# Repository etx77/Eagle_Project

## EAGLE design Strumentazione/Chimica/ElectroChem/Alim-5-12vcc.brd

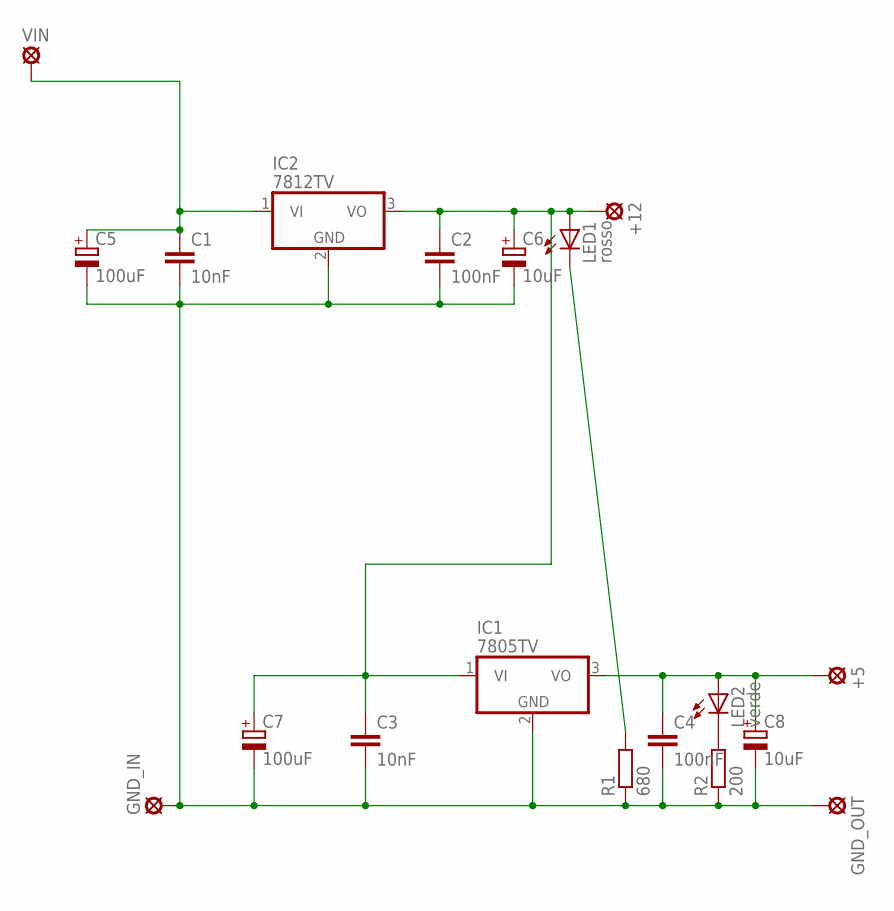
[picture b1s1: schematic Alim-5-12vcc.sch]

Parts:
+5, +12: SE14
C1, C3: 10nF; C050-025X075
C2, C4: 100nF; C050-025X075
C5, C7: 100uF; E2,5-6
C6, C8: 10uF; E2,5-6
GND_IN: SE14
GND_OUT: SE14
IC1: 7805TV; TO220V
IC2: 7812TV; TO220V
LED1: rosso; LED5MM
LED2: verde; LED5MM
R1: 680; 0204/7
R2: 200; 0204/7
VIN: SE14

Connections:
unnamed: C1.1, C5.+, IC2.1 (VI), VIN.MP
unnamed: +12.MP, C2.1, C3.1, C6.+, C7.+, IC1.1 (VI), IC2.3 (VO), LED1.A
unnamed: C1.2, C2.2, C3.2, C4.2, C5.-, C6.-, C7.-, C8.-, GND_IN.MP, GND_OUT.MP, IC1.2 (GND), IC2.2 (GND), R1.1, R2.1
unnamed: LED1.K (C), R1.2
unnamed: +5.MP, C4.1, C8.+, IC1.3 (VO), LED2.A
unnamed: LED2.K (C), R2.2

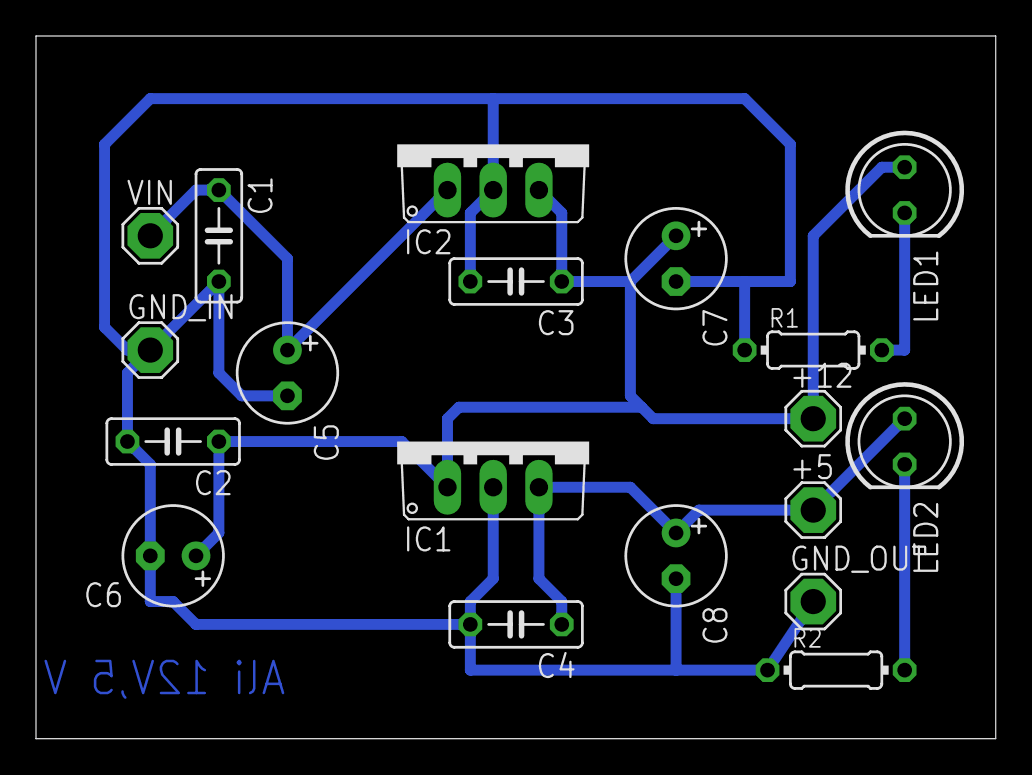
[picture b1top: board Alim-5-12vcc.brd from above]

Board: 2 copper layers, 53.3 x 39.0 mm, 19 parts (0 on the bottom side), 6 nets.

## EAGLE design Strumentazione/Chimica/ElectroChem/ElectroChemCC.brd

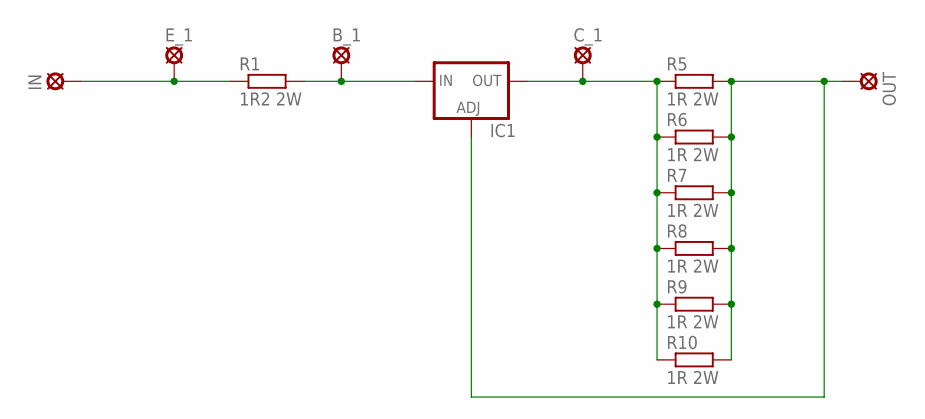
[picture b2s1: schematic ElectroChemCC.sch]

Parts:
B_1: SE14
C_1: SE14
E_1: SE14
IC1: LM317TS; 317TS
IN: SE14
OUT: SE14
R1: 1R2 2W; 0207/10
R5, R6, R7, R8, R9, R10: 1R 2W; 0617/22

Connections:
unnamed: IC1.1 (ADJ), OUT.MP, R5.2, R6.2, R7.2, R8.2, R9.2, R10.2
unnamed: E_1.MP, IN.MP, R1.1
unnamed: C_1.MP, IC1.2 (OUT), R5.1, R6.1, R7.1, R8.1, R9.1, R10.1
unnamed: B_1.MP, IC1.3 (IN), R1.2

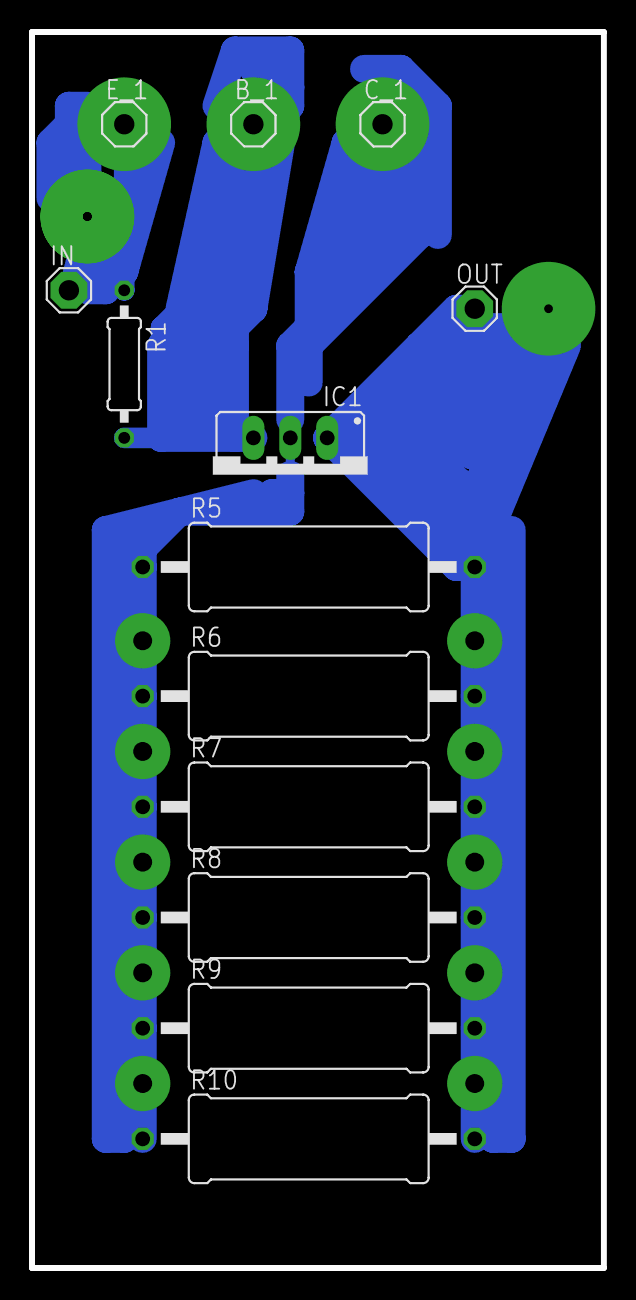
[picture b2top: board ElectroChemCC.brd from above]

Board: 2 copper layers, 39.4 x 85.1 mm, 13 parts (0 on the bottom side), 4 nets.

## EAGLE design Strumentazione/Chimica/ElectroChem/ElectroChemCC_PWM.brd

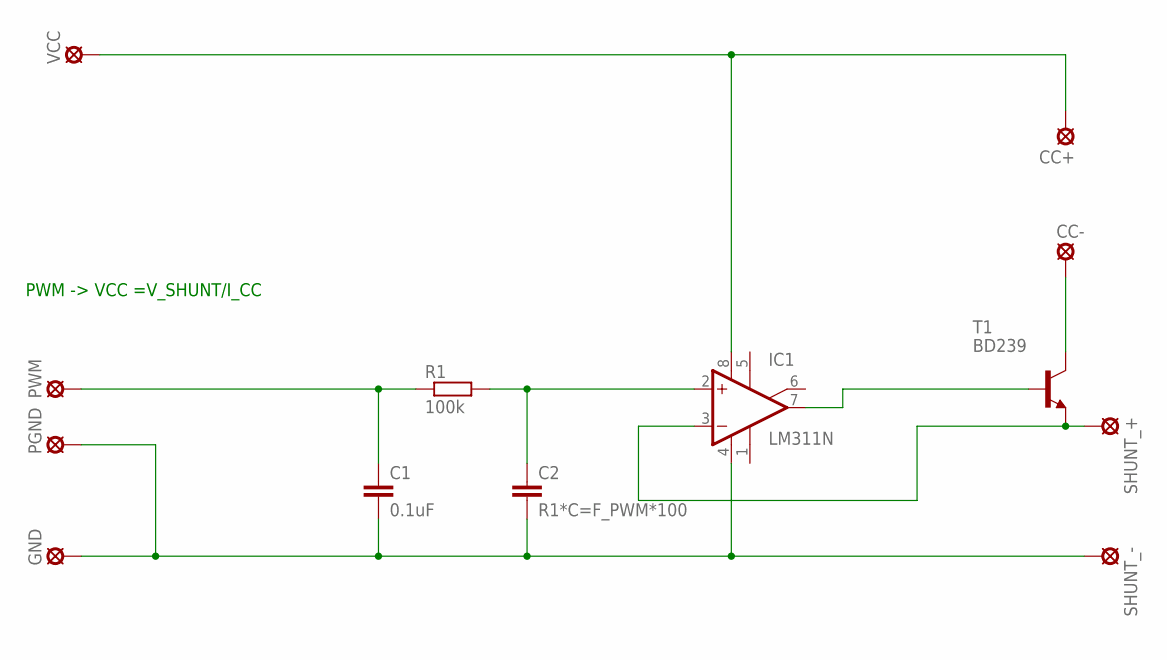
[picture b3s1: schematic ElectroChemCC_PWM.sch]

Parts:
C1: 0.1uF; C050-025X075
C2: R1*C=F_PWM*100; C050-025X075
CC+: LSP10
CC-: LSP10
GND: LSP10
IC1: LM311N; DIL08
PGND: LSP10
PWM: LSP10
R1: 100k; 0207/10
SHUNT_+: LSP10
SHUNT_-: LSP10
T1: BD239; TO220
VCC: LSP10

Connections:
unnamed: CC+.MP, IC1.8 (V+), VCC.MP
unnamed: C1.2, C2.2, GND.MP, IC1.4 (V-), PGND.MP, SHUNT_-.MP
unnamed: C1.1, PWM.MP, R1.1
unnamed: C2.1, IC1.2 (+IN), R1.2
unnamed: IC1.7 (OUT), T1.1 (B)
unnamed: CC-.MP, T1.2 (C)
unnamed: IC1.3 (-IN), SHUNT_+.MP, T1.3 (E)

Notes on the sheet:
PWM -> VCC =V_SHUNT/I_CC

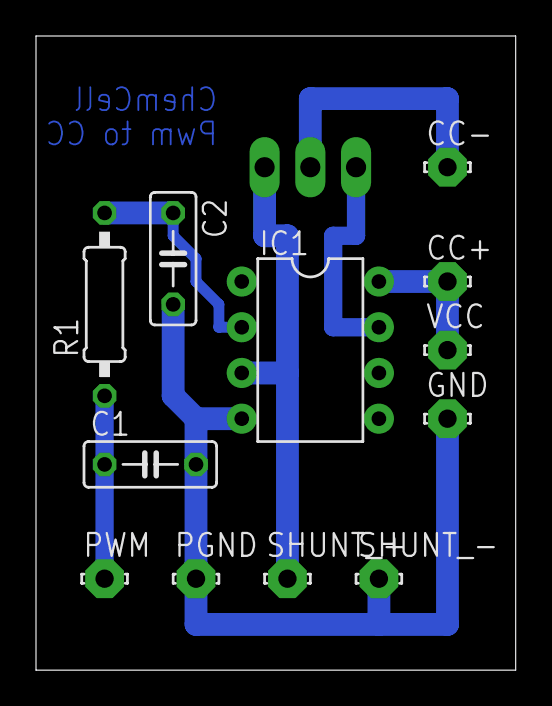
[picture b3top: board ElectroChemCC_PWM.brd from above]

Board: 2 copper layers, 26.6 x 35.2 mm, 13 parts (1 on the bottom side), 7 nets.

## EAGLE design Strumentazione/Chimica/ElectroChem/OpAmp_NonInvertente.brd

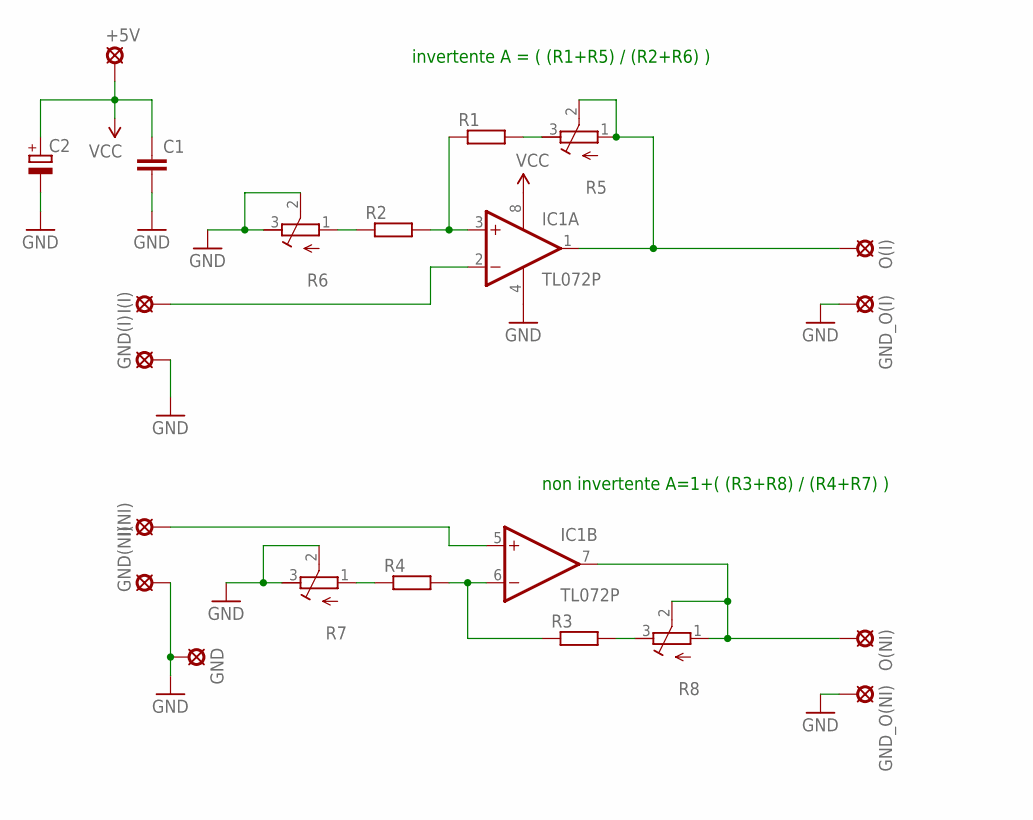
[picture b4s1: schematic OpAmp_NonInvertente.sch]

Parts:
+5V: LSP10
C1: C-EU025-024X044; C025-024X044
C2: CPOL-EUE2.5-6; E2,5-6
GND: LSP10
GND(I): LSP10
GND(NI): LSP10
GND_O(I): LSP10
GND_O(NI): LSP10
I(I): LSP10
I(NI): LSP10
IC1: TL072P; DIL08
O(I): LSP10
O(NI): LSP10
R1, R2, R3, R4: R-EU_0309/10; 0309/10
R5, R6, R7, R8: R-TRIMM3339P; RTRIM3339P

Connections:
GND: C1.2, C2.-, GND.MP, GND(I).MP, GND(NI).MP, GND_O(I).MP, GND_O(NI).MP, IC1.4 (V-), R6.2 (S), R6.3 (E), R7.2 (S), R7.3 (E)
unnamed: R2.1, R6.1 (A)
unnamed: IC1.3 (+IN), R1.1, R2.2
unnamed: R1.2, R5.3 (E)
unnamed: IC1.1 (OUT), O(I).MP, R5.1 (A), R5.2 (S)
unnamed: IC1.6 (-IN), R3.1, R4.2
unnamed: R4.1, R7.1 (A)
unnamed: R3.2, R8.3 (E)
unnamed: IC1.7 (OUT), O(NI).MP, R8.1 (A), R8.2 (S)
unnamed: I(NI).MP, IC1.5 (+IN)
unnamed: I(I).MP, IC1.2 (-IN)
VCC: +5V.MP, C1.1, C2.+, IC1.8 (V+)

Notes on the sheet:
invertente A = ( (R1+R5) / (R2+R6) )
non invertente A=1+( (R3+R8) / (R4+R7) )

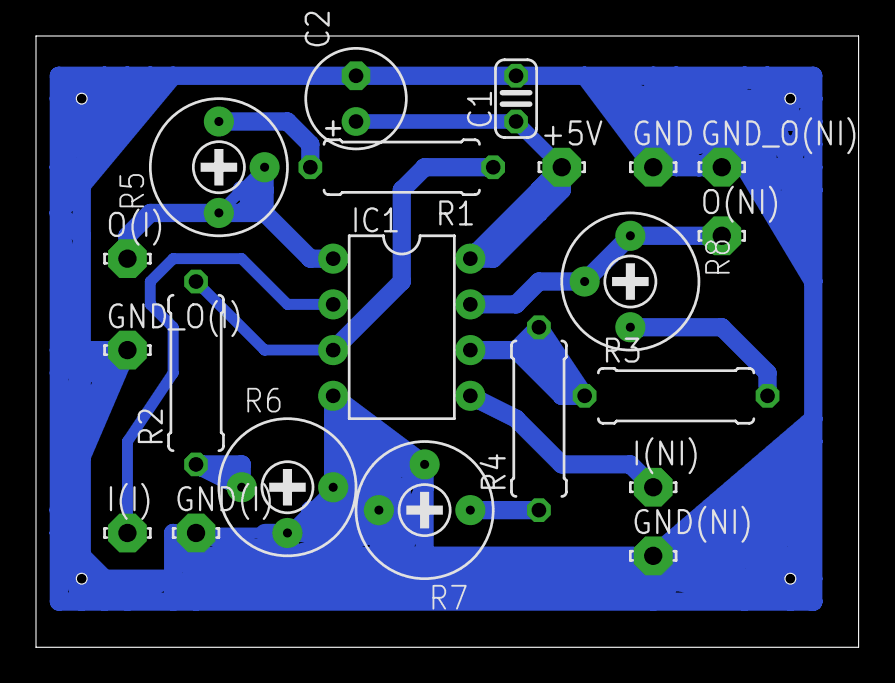
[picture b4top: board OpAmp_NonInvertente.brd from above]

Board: 2 copper layers, 45.7 x 34.0 mm, 21 parts (0 on the bottom side), 12 nets.

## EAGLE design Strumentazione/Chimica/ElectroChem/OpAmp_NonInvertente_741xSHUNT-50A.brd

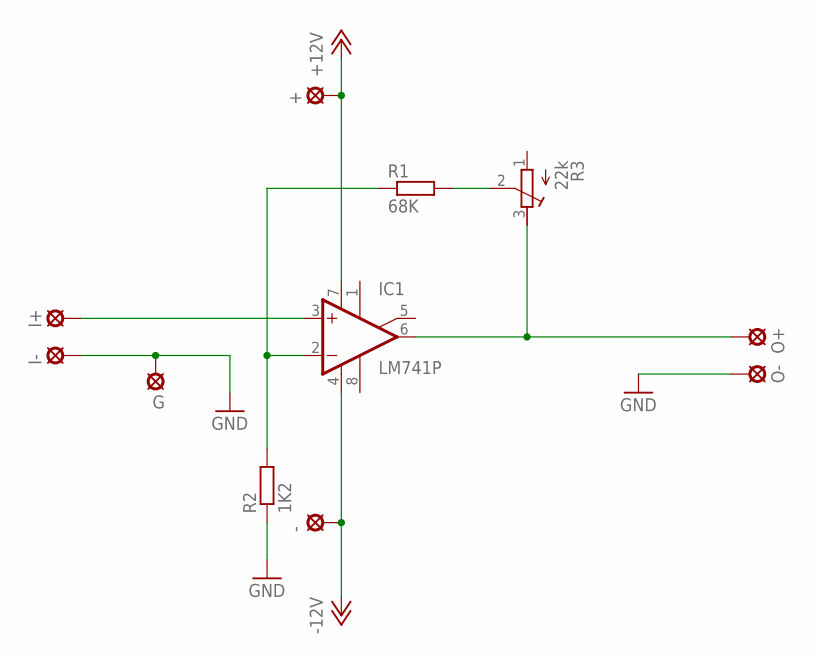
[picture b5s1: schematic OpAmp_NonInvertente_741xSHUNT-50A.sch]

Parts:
+: LSP10
-: LSP10
G: LSP10
I+: LSP10
I-: LSP10
IC1: LM741P; DIL08
O+: LSP10
O-: LSP10
R1: 68K; 0207/12
R2: 1K2; 0207/12
R3: 22k; RTRIM3339P

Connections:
+12V: +.MP, IC1.7 (V+)
-12V: -.MP, IC1.4 (V-)
GND: G.MP, I-.MP, O-.MP, R2.1
unnamed: IC1.2 (-IN), R1.1, R2.2
unnamed: R1.2, R3.2 (S)
unnamed: IC1.6 (OUT), O+.MP, R3.3 (E)
unnamed: I+.MP, IC1.3 (+IN)

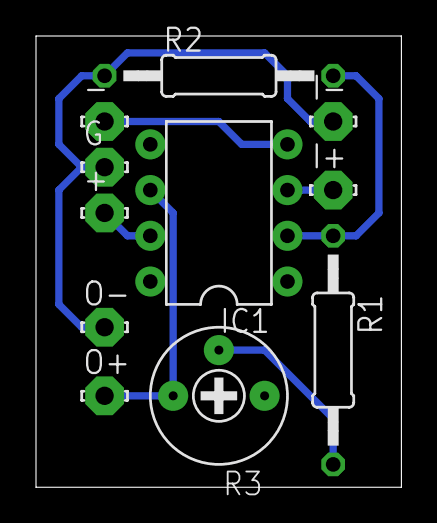
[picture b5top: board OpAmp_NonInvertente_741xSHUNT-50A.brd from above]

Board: 2 copper layers, 20.3 x 25.1 mm, 11 parts (0 on the bottom side), 7 nets.

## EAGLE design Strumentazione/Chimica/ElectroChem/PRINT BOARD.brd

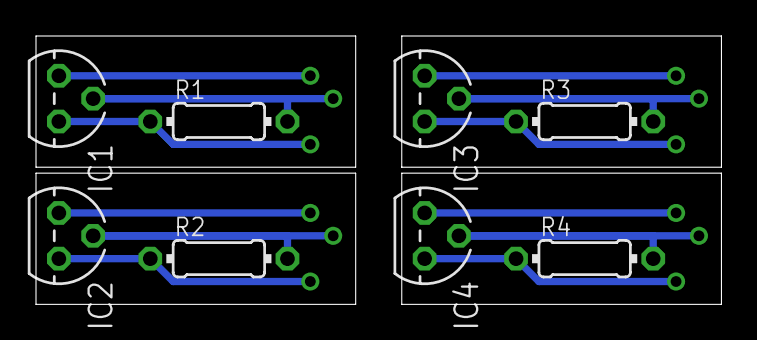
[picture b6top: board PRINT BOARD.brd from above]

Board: 2 copper layers, 38.1 x 14.9 mm, 8 parts (0 on the bottom side), 8 nets.

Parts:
IC1, IC2, IC3, IC4: LM35CZ; TO92
R1, R2, R3, R4: 100k; 0204/7

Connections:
unnamed: IC1.3, R1.1
unnamed: IC1.2, R1.2
unnamed: IC2.3, R2.1
unnamed: IC2.2, R2.2
unnamed: IC3.3, R3.1
unnamed: IC3.2, R3.2
unnamed: IC4.3, R4.1
unnamed: IC4.2, R4.2

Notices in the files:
parts and their libraries:
SparkFun-Aesthetics: Licensing: Creative Commons ShareAlike 4.0 International - https://creativecommons.org/licenses/by-sa/4.0
